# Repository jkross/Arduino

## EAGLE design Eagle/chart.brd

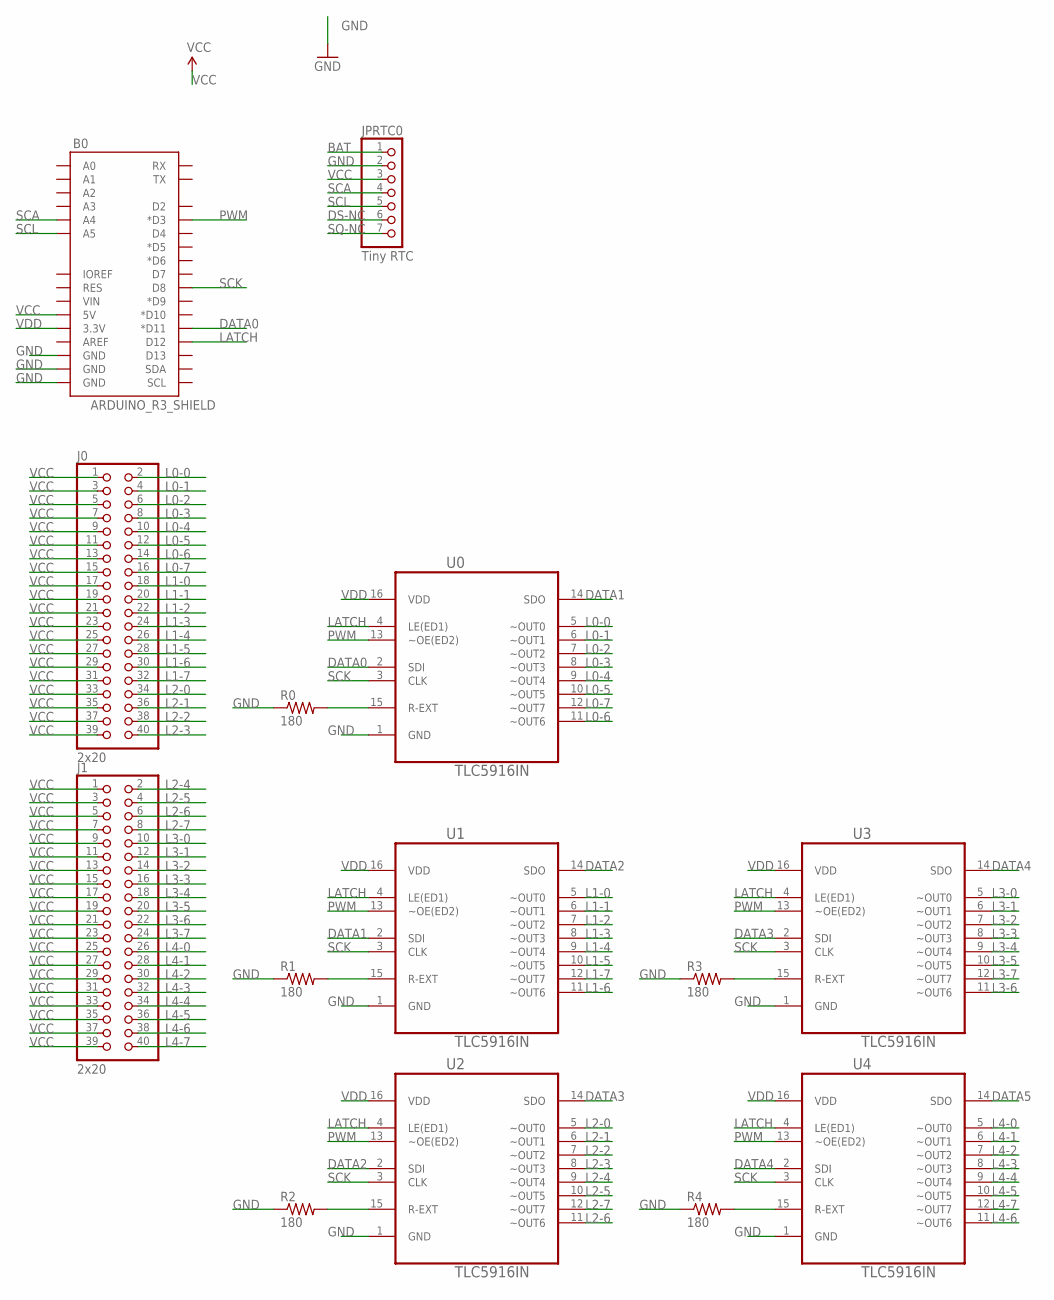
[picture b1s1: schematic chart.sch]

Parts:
B0: ARDUINO_R3_SHIELD; UNO_R3_SHIELD
J0, J1: 2x20; 2X20/90
JPRTC0: Tiny RTC; 1X07
R0, R1, R2, R3, R4: 180; AXIAL-0.4
U0, U1, U2, U3, U4: TLC5916IN; DIP254P762X508-16

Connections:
BAT: JPRTC0.1
DATA0: B0.D11 (*D11), U0.2 (SDI)
DATA1: U0.14 (SDO), U1.2 (SDI)
DATA2: U1.14 (SDO), U2.2 (SDI)
DATA3: U2.14 (SDO), U3.2 (SDI)
DATA4: U3.14 (SDO), U4.2 (SDI)
DATA5: U4.14 (SDO)
DS-NC: JPRTC0.6
GND: B0.GND@0 (GND), B0.GND@1 (GND), B0.GND@2 (GND), JPRTC0.2, R0.P$1 (1), R1.P$1 (1), R2.P$1 (1), R3.P$1 (1), R4.P$1 (1), U0.1 (GND), U1.1 (GND), U2.1 (GND), U3.1 (GND), U4.1 (GND)
L0-0: J0.2, U0.5 (~OUT0)
L0-1: J0.4, U0.6 (~OUT1)
L0-2: J0.6, U0.7 (~OUT2)
L0-3: J0.8, U0.8 (~OUT3)
L0-4: J0.10, U0.9 (~OUT4)
L0-5: J0.12, U0.10 (~OUT5)
L0-6: J0.14, U0.11 (~OUT6)
L0-7: J0.16, U0.12 (~OUT7)
L1-0: J0.18, U1.5 (~OUT0)
L1-1: J0.20, U1.6 (~OUT1)
L1-2: J0.22, U1.7 (~OUT2)
L1-3: J0.24, U1.8 (~OUT3)
L1-4: J0.26, U1.9 (~OUT4)
L1-5: J0.28, U1.10 (~OUT5)
L1-6: J0.30, U1.11 (~OUT6)
L1-7: J0.32, U1.12 (~OUT7)
L2-0: J0.34, U2.5 (~OUT0)
L2-1: J0.36, U2.6 (~OUT1)
L2-2: J0.38, U2.7 (~OUT2)
L2-3: J0.40, U2.8 (~OUT3)
L2-4: J1.2, U2.9 (~OUT4)
L2-5: J1.4, U2.10 (~OUT5)
L2-6: J1.6, U2.11 (~OUT6)
L2-7: J1.8, U2.12 (~OUT7)
L3-0: J1.10, U3.5 (~OUT0)
L3-1: J1.12, U3.6 (~OUT1)
L3-2: J1.14, U3.7 (~OUT2)
L3-3: J1.16, U3.8 (~OUT3)
L3-4: J1.18, U3.9 (~OUT4)
L3-5: J1.20, U3.10 (~OUT5)
L3-6: J1.22, U3.11 (~OUT6)
L3-7: J1.24, U3.12 (~OUT7)
L4-0: J1.26, U4.5 (~OUT0)
L4-1: J1.28, U4.6 (~OUT1)
L4-2: J1.30, U4.7 (~OUT2)
L4-3: J1.32, U4.8 (~OUT3)
L4-4: J1.34, U4.9 (~OUT4)
L4-5: J1.36, U4.10 (~OUT5)
L4-6: J1.38, U4.11 (~OUT6)
L4-7: J1.40, U4.12 (~OUT7)
LATCH: B0.D12, U0.4 (LE(ED1)), U1.4 (LE(ED1)), U2.4 (LE(ED1)), U3.4 (LE(ED1)), U4.4 (LE(ED1))
unnamed: R1.P$2 (2), U1.15 (R-EXT)
unnamed: R2.P$2 (2), U2.15 (R-EXT)
unnamed: R3.P$2 (2), U3.15 (R-EXT)
unnamed: R4.P$2 (2), U4.15 (R-EXT)
unnamed: R0.P$2 (2), U0.15 (R-EXT)
PWM: B0.D3 (*D3), U0.13 (~OE(ED2)), U1.13 (~OE(ED2)), U2.13 (~OE(ED2)), U3.13 (~OE(ED2)), U4.13 (~OE(ED2))
SCA: B0.A4, JPRTC0.4
SCK: B0.D8, U0.3 (CLK), U1.3 (CLK), U2.3 (CLK), U3.3 (CLK), U4.3 (CLK)
SCL: B0.A5, JPRTC0.5
SQ-NC: JPRTC0.7
VCC: B0.5V, J0.1, J0.3, J0.5, J0.7, J0.9, J0.11, J0.13, J0.15, J0.17, J0.19, J0.21, J0.23, J0.25, J0.27, J0.29, J0.31, J0.33, J0.35, J0.37, J0.39, J1.1, J1.3, J1.5, J1.7, J1.9, J1.11, J1.13, J1.15, J1.17, J1.19, J1.21, J1.23, J1.25, J1.27, J1.29, J1.31, J1.33, J1.35, J1.37, J1.39, JPRTC0.3
VDD: B0.3.3V, U0.16 (VDD), U1.16 (VDD), U2.16 (VDD), U3.16 (VDD), U4.16 (VDD)

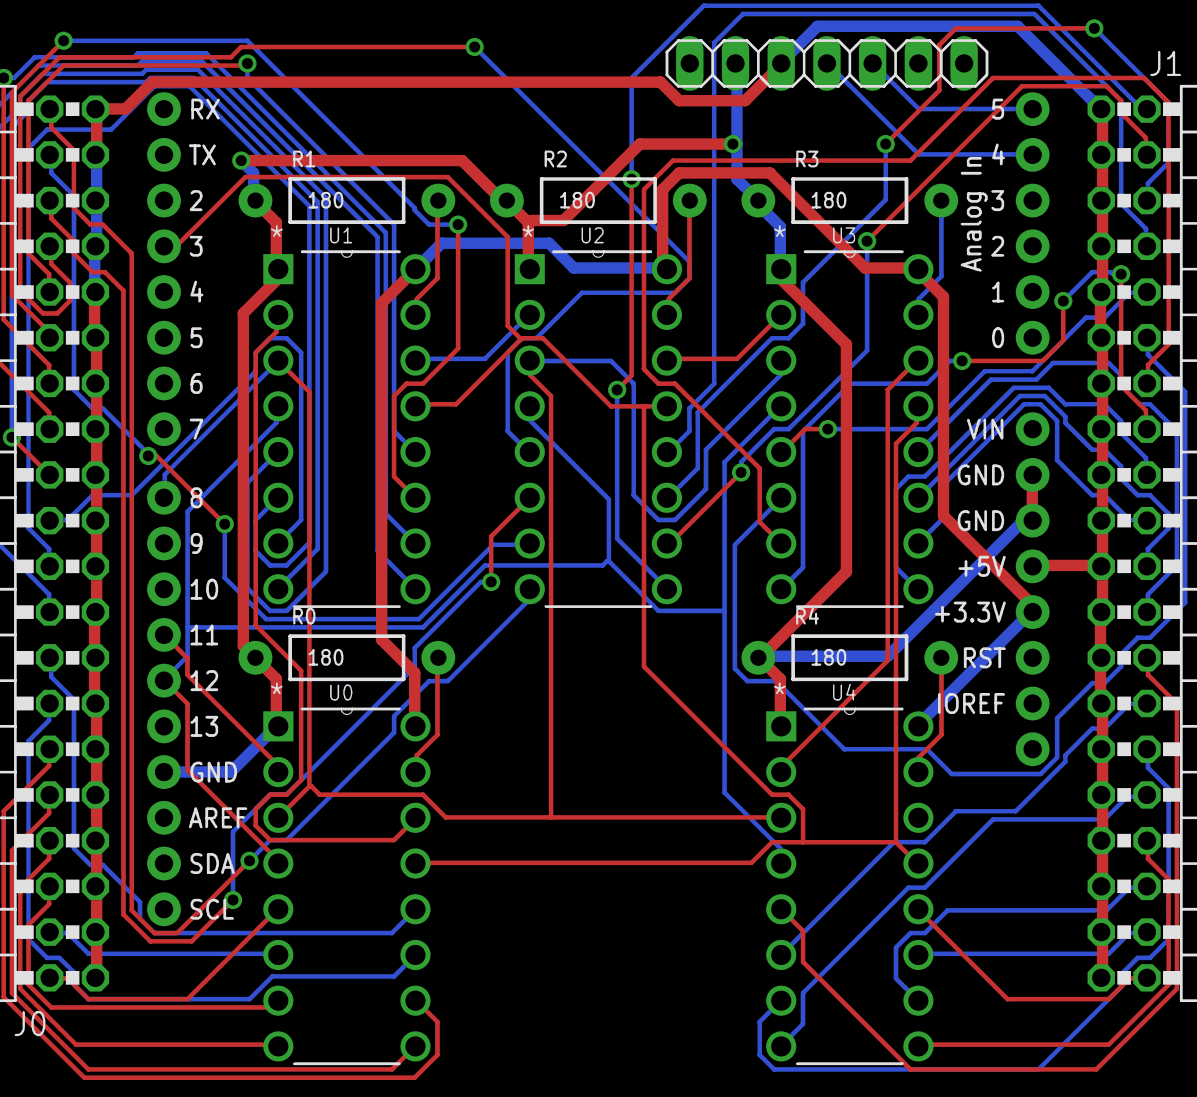
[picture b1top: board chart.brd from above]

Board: 2 copper layers, 14 parts (0 on the bottom side), 58 nets.

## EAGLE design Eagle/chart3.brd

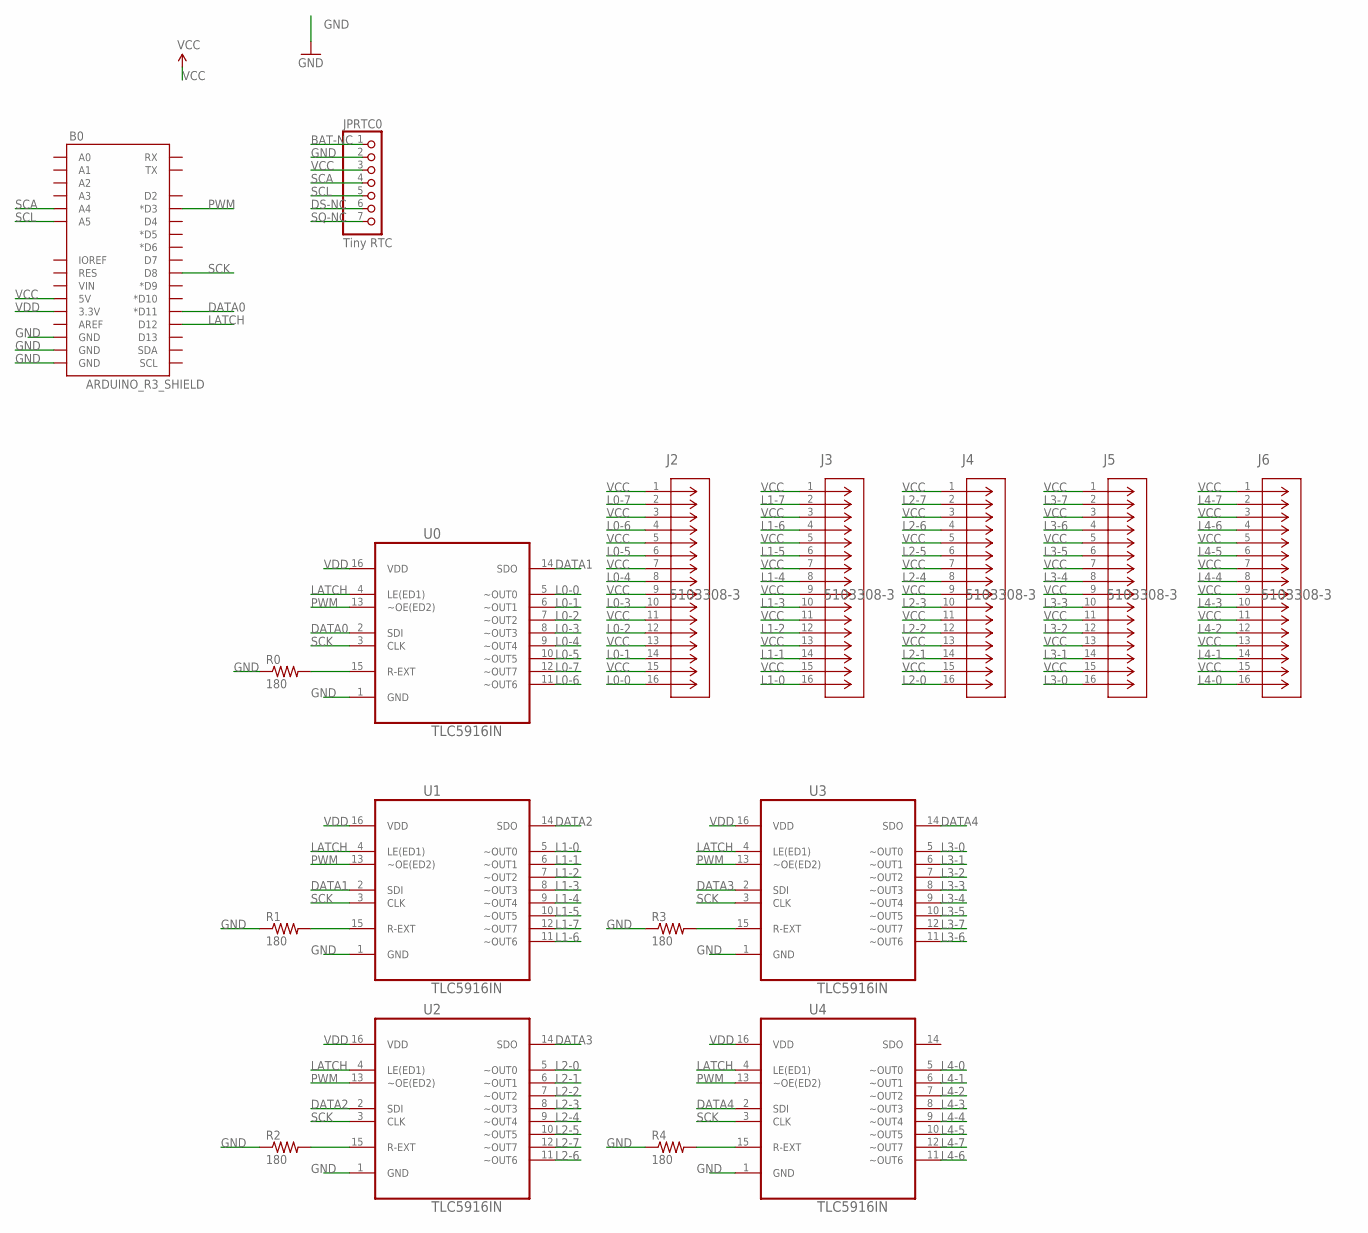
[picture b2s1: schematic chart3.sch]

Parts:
B0: ARDUINO_R3_SHIELD; UNO_R3_SHIELD
J2, J3, J4, J5, J6: 5103308-3; CON16_2X8_S4
JPRTC0: Tiny RTC; 1X07
R0, R1, R2, R3, R4: 180; AXIAL-0.4
U0, U1, U2, U3, U4: TLC5916IN; DIP254P762X508-16

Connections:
BAT-NC: JPRTC0.1
DATA0: B0.D11 (*D11), U0.2 (SDI)
DATA1: U0.14 (SDO), U1.2 (SDI)
DATA2: U1.14 (SDO), U2.2 (SDI)
DATA3: U2.14 (SDO), U3.2 (SDI)
DATA4: U3.14 (SDO), U4.2 (SDI)
DS-NC: JPRTC0.6
GND: B0.GND@0 (GND), B0.GND@1 (GND), B0.GND@2 (GND), JPRTC0.2, R0.P$1 (1), R1.P$1 (1), R2.P$1 (1), R3.P$1 (1), R4.P$1 (1), U0.1 (GND), U1.1 (GND), U2.1 (GND), U3.1 (GND), U4.1 (GND)
L0-0: J2.16, U0.5 (~OUT0)
L0-1: J2.14, U0.6 (~OUT1)
L0-2: J2.12, U0.7 (~OUT2)
L0-3: J2.10, U0.8 (~OUT3)
L0-4: J2.8, U0.9 (~OUT4)
L0-5: J2.6, U0.10 (~OUT5)
L0-6: J2.4, U0.11 (~OUT6)
L0-7: J2.2, U0.12 (~OUT7)
L1-0: J3.16, U1.5 (~OUT0)
L1-1: J3.14, U1.6 (~OUT1)
L1-2: J3.12, U1.7 (~OUT2)
L1-3: J3.10, U1.8 (~OUT3)
L1-4: J3.8, U1.9 (~OUT4)
L1-5: J3.6, U1.10 (~OUT5)
L1-6: J3.4, U1.11 (~OUT6)
L1-7: J3.2, U1.12 (~OUT7)
L2-0: J4.16, U2.5 (~OUT0)
L2-1: J4.14, U2.6 (~OUT1)
L2-2: J4.12, U2.7 (~OUT2)
L2-3: J4.10, U2.8 (~OUT3)
L2-4: J4.8, U2.9 (~OUT4)
L2-5: J4.6, U2.10 (~OUT5)
L2-6: J4.4, U2.11 (~OUT6)
L2-7: J4.2, U2.12 (~OUT7)
L3-0: J5.16, U3.5 (~OUT0)
L3-1: J5.14, U3.6 (~OUT1)
L3-2: J5.12, U3.7 (~OUT2)
L3-3: J5.10, U3.8 (~OUT3)
L3-4: J5.8, U3.9 (~OUT4)
L3-5: J5.6, U3.10 (~OUT5)
L3-6: J5.4, U3.11 (~OUT6)
L3-7: J5.2, U3.12 (~OUT7)
L4-0: J6.16, U4.5 (~OUT0)
L4-1: J6.14, U4.6 (~OUT1)
L4-2: J6.12, U4.7 (~OUT2)
L4-3: J6.10, U4.8 (~OUT3)
L4-4: J6.8, U4.9 (~OUT4)
L4-5: J6.6, U4.10 (~OUT5)
L4-6: J6.4, U4.11 (~OUT6)
L4-7: J6.2, U4.12 (~OUT7)
LATCH: B0.D12, U0.4 (LE(ED1)), U1.4 (LE(ED1)), U2.4 (LE(ED1)), U3.4 (LE(ED1)), U4.4 (LE(ED1))
unnamed: R1.P$2 (2), U1.15 (R-EXT)
unnamed: R2.P$2 (2), U2.15 (R-EXT)
unnamed: R3.P$2 (2), U3.15 (R-EXT)
unnamed: R4.P$2 (2), U4.15 (R-EXT)
unnamed: R0.P$2 (2), U0.15 (R-EXT)
PWM: B0.D3 (*D3), U0.13 (~OE(ED2)), U1.13 (~OE(ED2)), U2.13 (~OE(ED2)), U3.13 (~OE(ED2)), U4.13 (~OE(ED2))
SCA: B0.A4, JPRTC0.4
SCK: B0.D8, U0.3 (CLK), U1.3 (CLK), U2.3 (CLK), U3.3 (CLK), U4.3 (CLK)
SCL: B0.A5, JPRTC0.5
SQ-NC: JPRTC0.7
VCC: B0.5V, J2.1, J2.3, J2.5, J2.7, J2.9, J2.11, J2.13, J2.15, J3.1, J3.3, J3.5, J3.7, J3.9, J3.11, J3.13, J3.15, J4.1, J4.3, J4.5, J4.7, J4.9, J4.11, J4.13, J4.15, J5.1, J5.3, J5.5, J5.7, J5.9, J5.11, J5.13, J5.15, J6.1, J6.3, J6.5, J6.7, J6.9, J6.11, J6.13, J6.15, JPRTC0.3
VDD: B0.3.3V, U0.16 (VDD), U1.16 (VDD), U2.16 (VDD), U3.16 (VDD), U4.16 (VDD)

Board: 2 copper layers, 17 parts (0 on the bottom side), 58 nets, no tracks yet.

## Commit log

2016-10-16 new part from Digikey
2016-10-16 remove EDA
2016-10-16 Organize
2016-10-17 Add Readme Files Organize files
2016-10-18 remove large unnecessary pdfs
2016-10-18 remove xml from other version
2017-11-08 prepre to move

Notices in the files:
parts and their libraries:
SparkFun-Boards: Licensing: Creative Commons ShareAlike 4.0 International - https://creativecommons.org/licenses/by-sa/4.0
COPYRIGHT: Copyright (C) 2015 Accelerated Designs. All rights reserved
